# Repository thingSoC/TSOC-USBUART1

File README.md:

# TSOC-USBUART1

**TSOC-USBUART1** is a USB to UART Base Board **thingSoC Reference Design.** 

**thingSoC Reference Designs** are example thingSoC implementations that implement
various reference and testing circuits for demonstrating the use of the thingSoC libraries.
These reference designs can serve as starting templates for user designs.

**TSOC-USBUART1** includes a single channel USB to Serial(UART) interface, 
and status LED's, as well as an "FTDI" pinout compatible connector.

[ 
*TSOC-USBUART1*](https://github.com/thingSoC/TSOC-USBUART1)

---------------------------------------

## TSOC-USBUART1 Status <a name="TSOC-USBUART1_status"/>

**01/13/2016:** 
Revision 3.1 - Revised USB ESD circuit to PA Standard USB2.0

**01/13/2016:** 
Revision 3.0 - NUF2221 ESD package pinout - PCB jumper with discrete resistors
Tested at 9600, 115200, 256000, 921600, 1843200 Baud rates

---------------------------------------

## TSOC-USBUART1 Documentation Index <a name="TSOC-USBUART1_documentation_index"/>

[TSOC-USBUART1 Project](http://thingsoc.github.io/projects/TSOC-USBUART1.html)

[TSOC-USBUART1 Hardware](https://github.com/thingSoC/TSOC-USBUART1/tree/master/TSOC-USBUART1/hardware)

---------------------------------------

## thingSoC Documentation Index <a name="thingSoC_documentation_index"/>

[thingSoC Organization Website](http://thingSoC.github.io)

[thingSoC FAQ - Frequently Asked Questions](http://thingsoc.github.io/support/faq.html)

---------------------------------------

[ 
*thingSoC*](http://thingsoc.github.io)

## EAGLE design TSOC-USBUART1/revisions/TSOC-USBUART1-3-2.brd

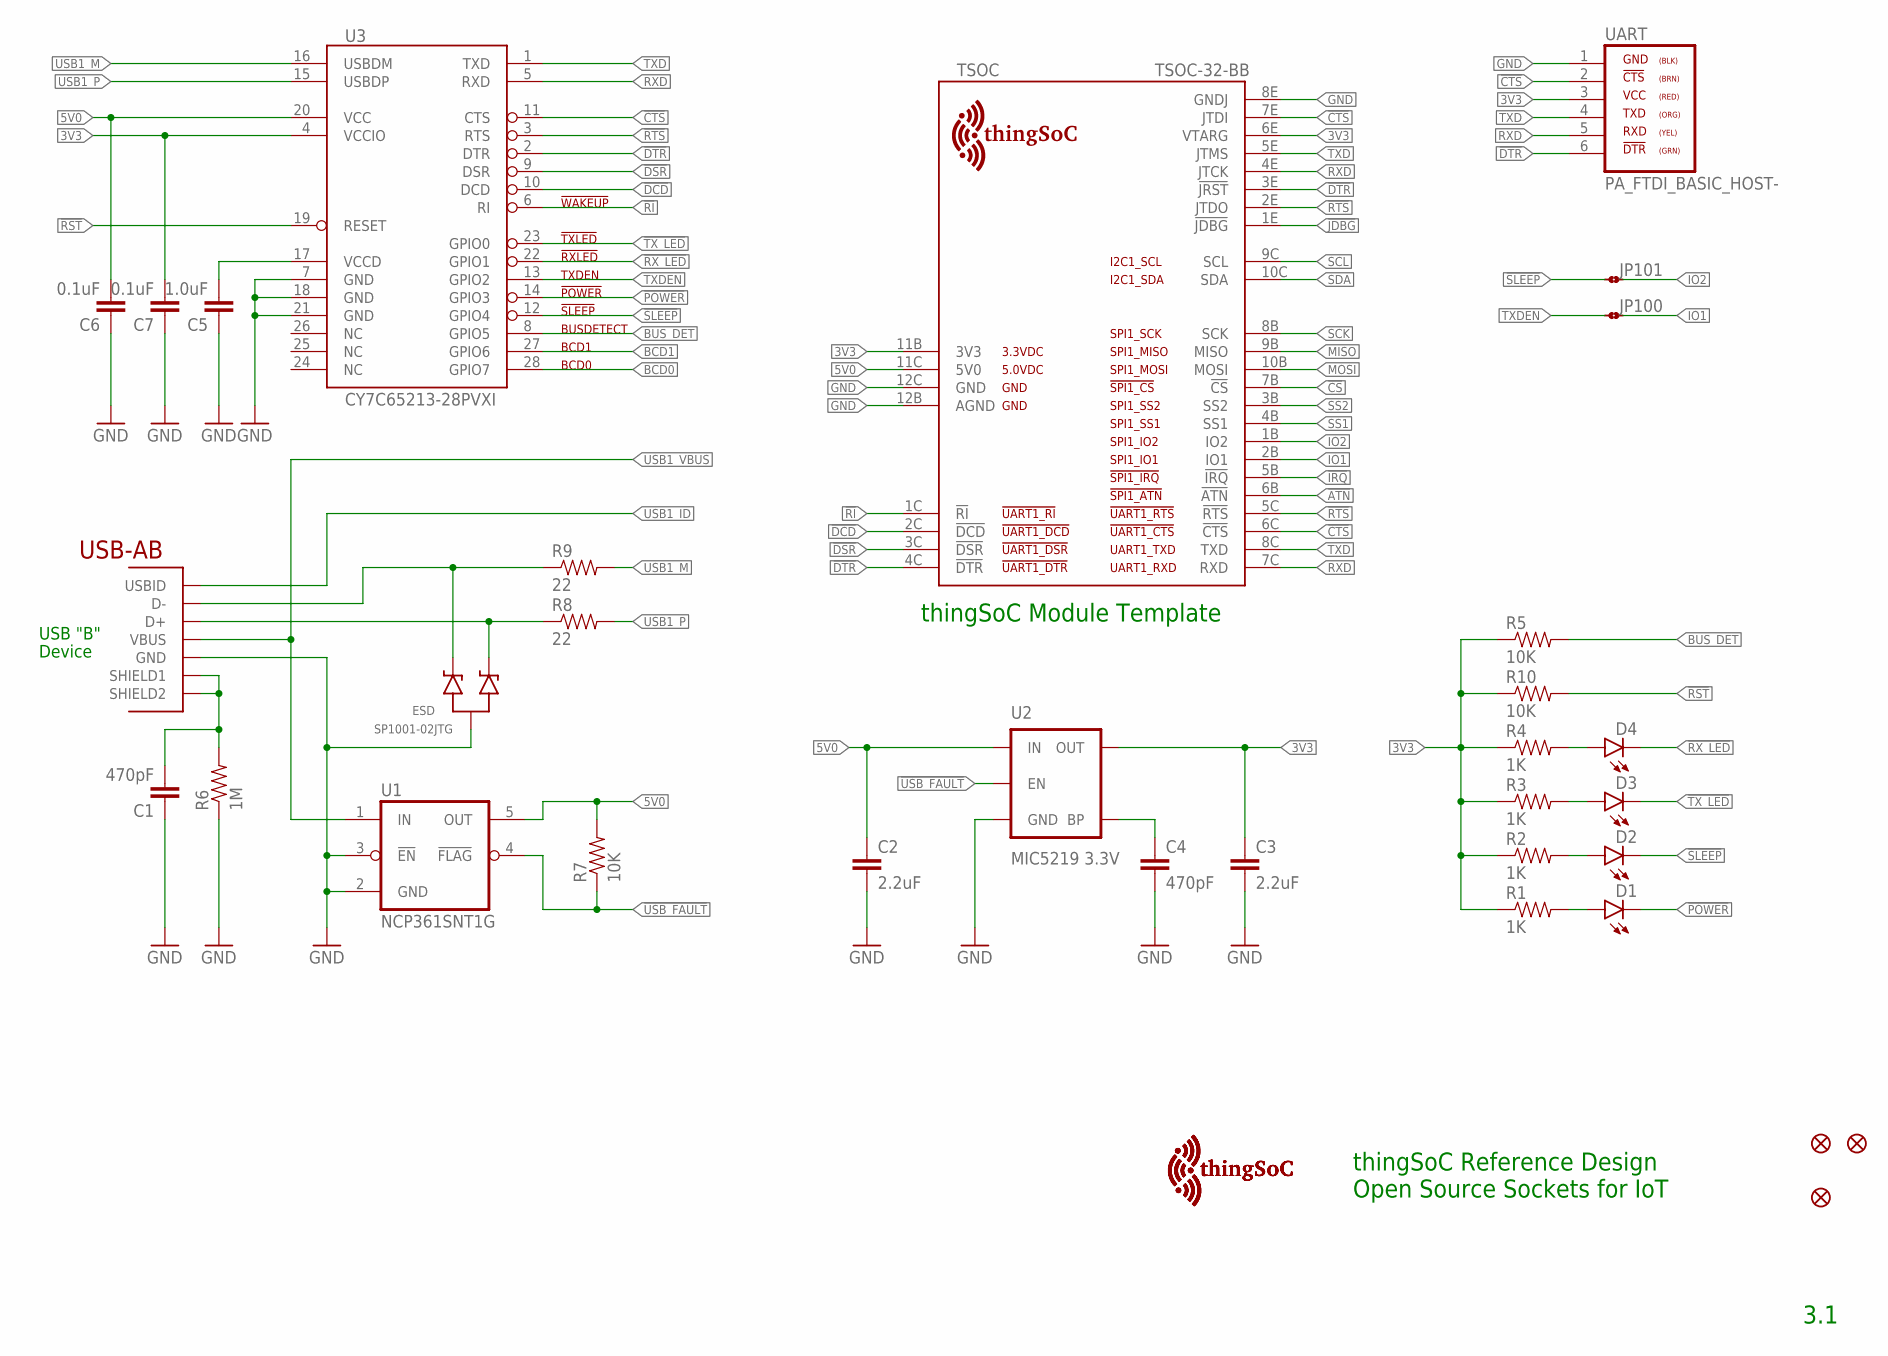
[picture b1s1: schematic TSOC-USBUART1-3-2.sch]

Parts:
C1, C4: 470pF; 0603-CAP
C2, C3: 2.2uF; 0603-CAP
C5: 1.0uF; 0603-CAP
C6, C7: 0.1uF; 0603-CAP
D1, D2, D3, D4: LED0603; LED-0603
ESD: SP1001-02JTG; SC70-3
FID1, FID2, FID3: FIDUCIAL1.5X3; FIDUCIAL-1.5X3
JP100, JP101: JMP-2-NO
R1, R2, R3, R4: 1K; 0603-RES
R5, R7, R10: 10K; 0603-RES
R6: 1M; 0603-RES
R8, R9: 22; 0603-RES
TSOC: TSOC-32-BB; TSOC-BB-S32
U1: NCP361SNT1G; SOP95P275X110-5N
U2: MIC5219 3.3V; SOT23-5
U3: CY7C65213-28PVXI; SSOP28DB
U$2, U$101: TSOC-LOGO-MED
UART: PA_FTDI_BASIC_HOST-; PA_FTDI_M5X1
USB1: USB_AB; USB-AB-MICRO-SMD

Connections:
3V3: C3.1, C7.2, R1.1, R2.1, R3.1, R4.1, R5.1, R10.1, TSOC.6E (VTARG), TSOC.11B (3V3), U2.5 (OUT), U3.4 (VCCIO), UART.3
5V0: C2.1, C6.2, R7.2, TSOC.11C (5V0), U1.5 (OUT), U2.1 (IN), U3.20 (VCC)
!ATN: TSOC.6B (!ATN)
!CS: TSOC.7B (!CS)
!CTS: TSOC.6C (!CTS), TSOC.7E (JTDI), U3.11 (CTS), UART.2
!DCD: TSOC.2C (!DCD), U3.10 (DCD)
!DSR: TSOC.3C (!DSR), U3.9 (DSR)
!DTR: TSOC.3E (!JRST), TSOC.4C (!DTR), U3.2 (DTR), UART.6
!IRQ: TSOC.5B (!IRQ)
!JDBG: TSOC.1E (!JDBG)
!POWER: D1.C, U3.14 (GPIO3)
!RI: TSOC.1C (!RI), U3.6 (RI)
!RST: R10.2, U3.19 (RESET)
!RTS: TSOC.2E (JTDO), TSOC.5C (!RTS), U3.3 (RTS)
!RX_LED: D4.C, U3.22 (GPIO1)
!SLEEP: D2.C, JP101.1, U3.12 (GPIO4)
!TX_LED: D3.C, U3.23 (GPIO0)
!USB_FAULT: R7.1, U1.4 (!FLAG), U2.3 (EN)
BCD0: U3.28 (GPIO7)
BCD1: U3.27 (GPIO6)
BLUE: D3.A, R3.2
BUS_DET: R5.2, U3.8 (GPIO5)
BYPASS: C4.1, U2.4 (BP)
GND: C1.1, C2.2, C3.2, C4.2, C5.1, C6.1, C7.1, ESD.3 (A), R6.1, TSOC.8E (GNDJ), TSOC.12B (AGND), TSOC.12C (GND), U1.2 (GND), U1.3 (!EN), U2.2 (GND), U3.7 (GND), U3.18 (GND), U3.21 (GND), UART.1, USB1.GND
GRN: D1.A, R1.2
IO1: JP100.2, TSOC.2B (IO1)
IO2: JP101.2, TSOC.1B (IO2)
MISO: TSOC.9B (MISO)
MOSI: TSOC.10B (MOSI)
RED: D2.A, R2.2
RXD: TSOC.4E (JTCK), TSOC.7C (RXD), U3.5 (RXD), UART.5
SCK: TSOC.8B (SCK)
SCL: TSOC.9C (SCL)
SDA: TSOC.10C (SDA)
SS1: TSOC.4B (SS1)
SS2: TSOC.3B (SS2)
TXD: TSOC.5E (JTMS), TSOC.8C (TXD), U3.1 (TXD), UART.4
TXDEN: JP100.1, U3.13 (GPIO2)
USB1_DM: ESD.2 (C2), R9.1, USB1.D-
USB1_DP: ESD.1 (C1), R8.1, USB1.D+
USB1_ID: USB1.ID (USBID)
USB1_M: R9.2, U3.16 (USBDM)
USB1_P: R8.2, U3.15 (USBDP)
USB1_SHIELD: C1.2, R6.2, USB1.SHIELD1, USB1.SHIELD2
USB1_VBUS: U1.1 (IN), USB1.VBUS
VCCD: C5.2, U3.17 (VCCD)
YEL: D4.A, R4.2

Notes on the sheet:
thingSoC Module Template
USB "B"
Device
thingSoC Reference Design Open Source Sockets for IoT
3.1

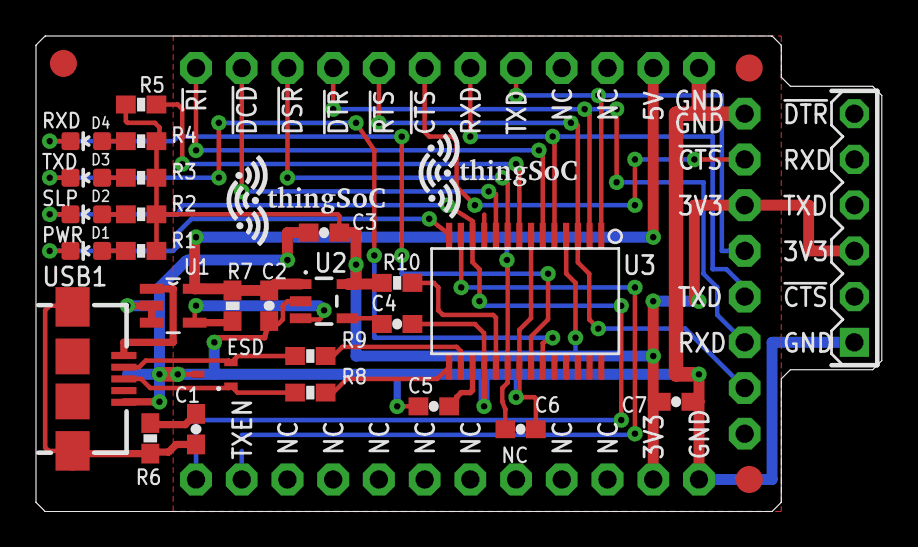
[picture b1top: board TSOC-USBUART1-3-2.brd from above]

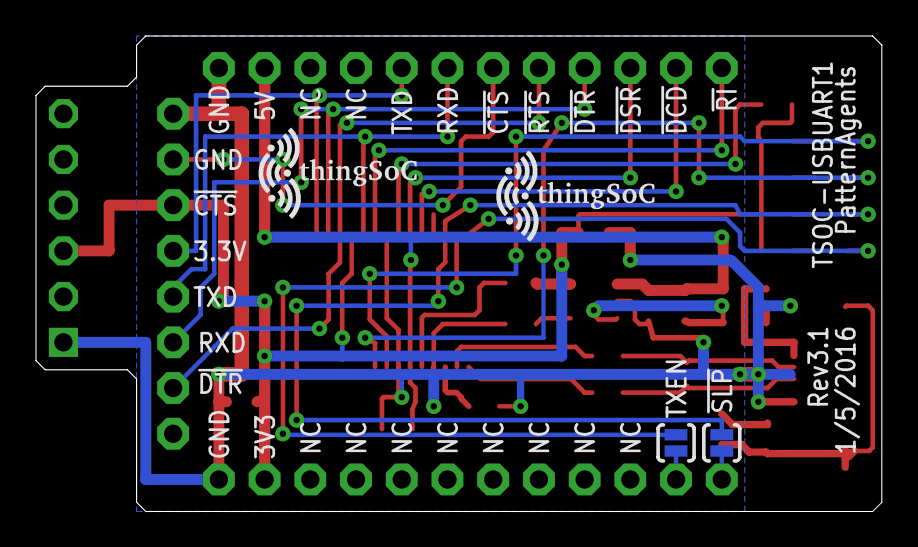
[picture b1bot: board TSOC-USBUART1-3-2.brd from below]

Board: 2 copper layers, 47.0 x 26.4 mm, 37 parts (4 on the bottom side), 33 nets.

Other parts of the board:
U$1, U$102: TSOC-LOGO-MED

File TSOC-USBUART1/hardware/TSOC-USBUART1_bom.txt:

/home/moxon/github/TSOC-USBUART1/TSOC-USBUART1/TSOC-USBUART1.sch (Revision 3.1)
----------------------------------------------------------------------------------------------
Qty Value               Device              Package               Parts            Description
----------------------------------------------------------------------------------------------
4   R/G/B/Y             LED0603             LED-0603              D1, D2, D3, D4   LEDs
2   0.1uF               CAP0603-CAP         0603-CAP              C6, C7           Capacitor
1   1.0uF               CAP0603-CAP         0603-CAP              C5               Capacitor
3   10K                 RESISTOR0603-RES    0603-RES              R5, R7, R10      Resistor
4   1K                  RESISTOR0603-RES    0603-RES              R1, R2, R3, R4   Resistor
1   1M                  RESISTOR0603-RES    0603-RES              R6               Resistor
2   2.2uF               CAP0603-CAP         0603-CAP              C2, C3           Capacitor
2   22                  RESISTOR0603-RES    0603-RES              R8, R9           Resistor
2   470pF               CAP0603-CAP         0603-CAP              C1, C4           Capacitor
1   CY7C65213-28PVXI    CY7C65213-28PVXI    SSOP28DB              U3               CY7C65213-28PVXI
1   MIC5219 3.3V        V_REG_MIC52193.3V   SOT23-5               U2               V_REG MIC5219
1   NCP361SNT1G         NCP361SNT1G         SOP95P275X110-5N      U1               USB Overvoltage Protection
1   PA_FTDI_BASIC_HOST- PA_FTDI_BASIC_HOST- PA_FTDI_M6X1          UART             6 Pin Female RA 0.1"
1   SP1001-02JTG        SP1001-02JTG        SC70-3                ESD              TVS Diode Array
1   USB_AB              USB_AB              USB-AB-MICRO-SMD      USB1             USB AB

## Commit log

2015-12-08 rebuild
2016-01-13 revision 3.1
2016-07-07 checkpoint/update

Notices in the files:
parts and their libraries:
thingSoC: License : http://creativecommons.org/licenses/by-sa/4.0
(Creative Commons 4.0)
PatternAgents-Interface: Source License : http://www.digilentinc.com/Pmods/licensing.cfm
PA Pattern License : http://creativecommons.org/licenses/by-sa/4.0
